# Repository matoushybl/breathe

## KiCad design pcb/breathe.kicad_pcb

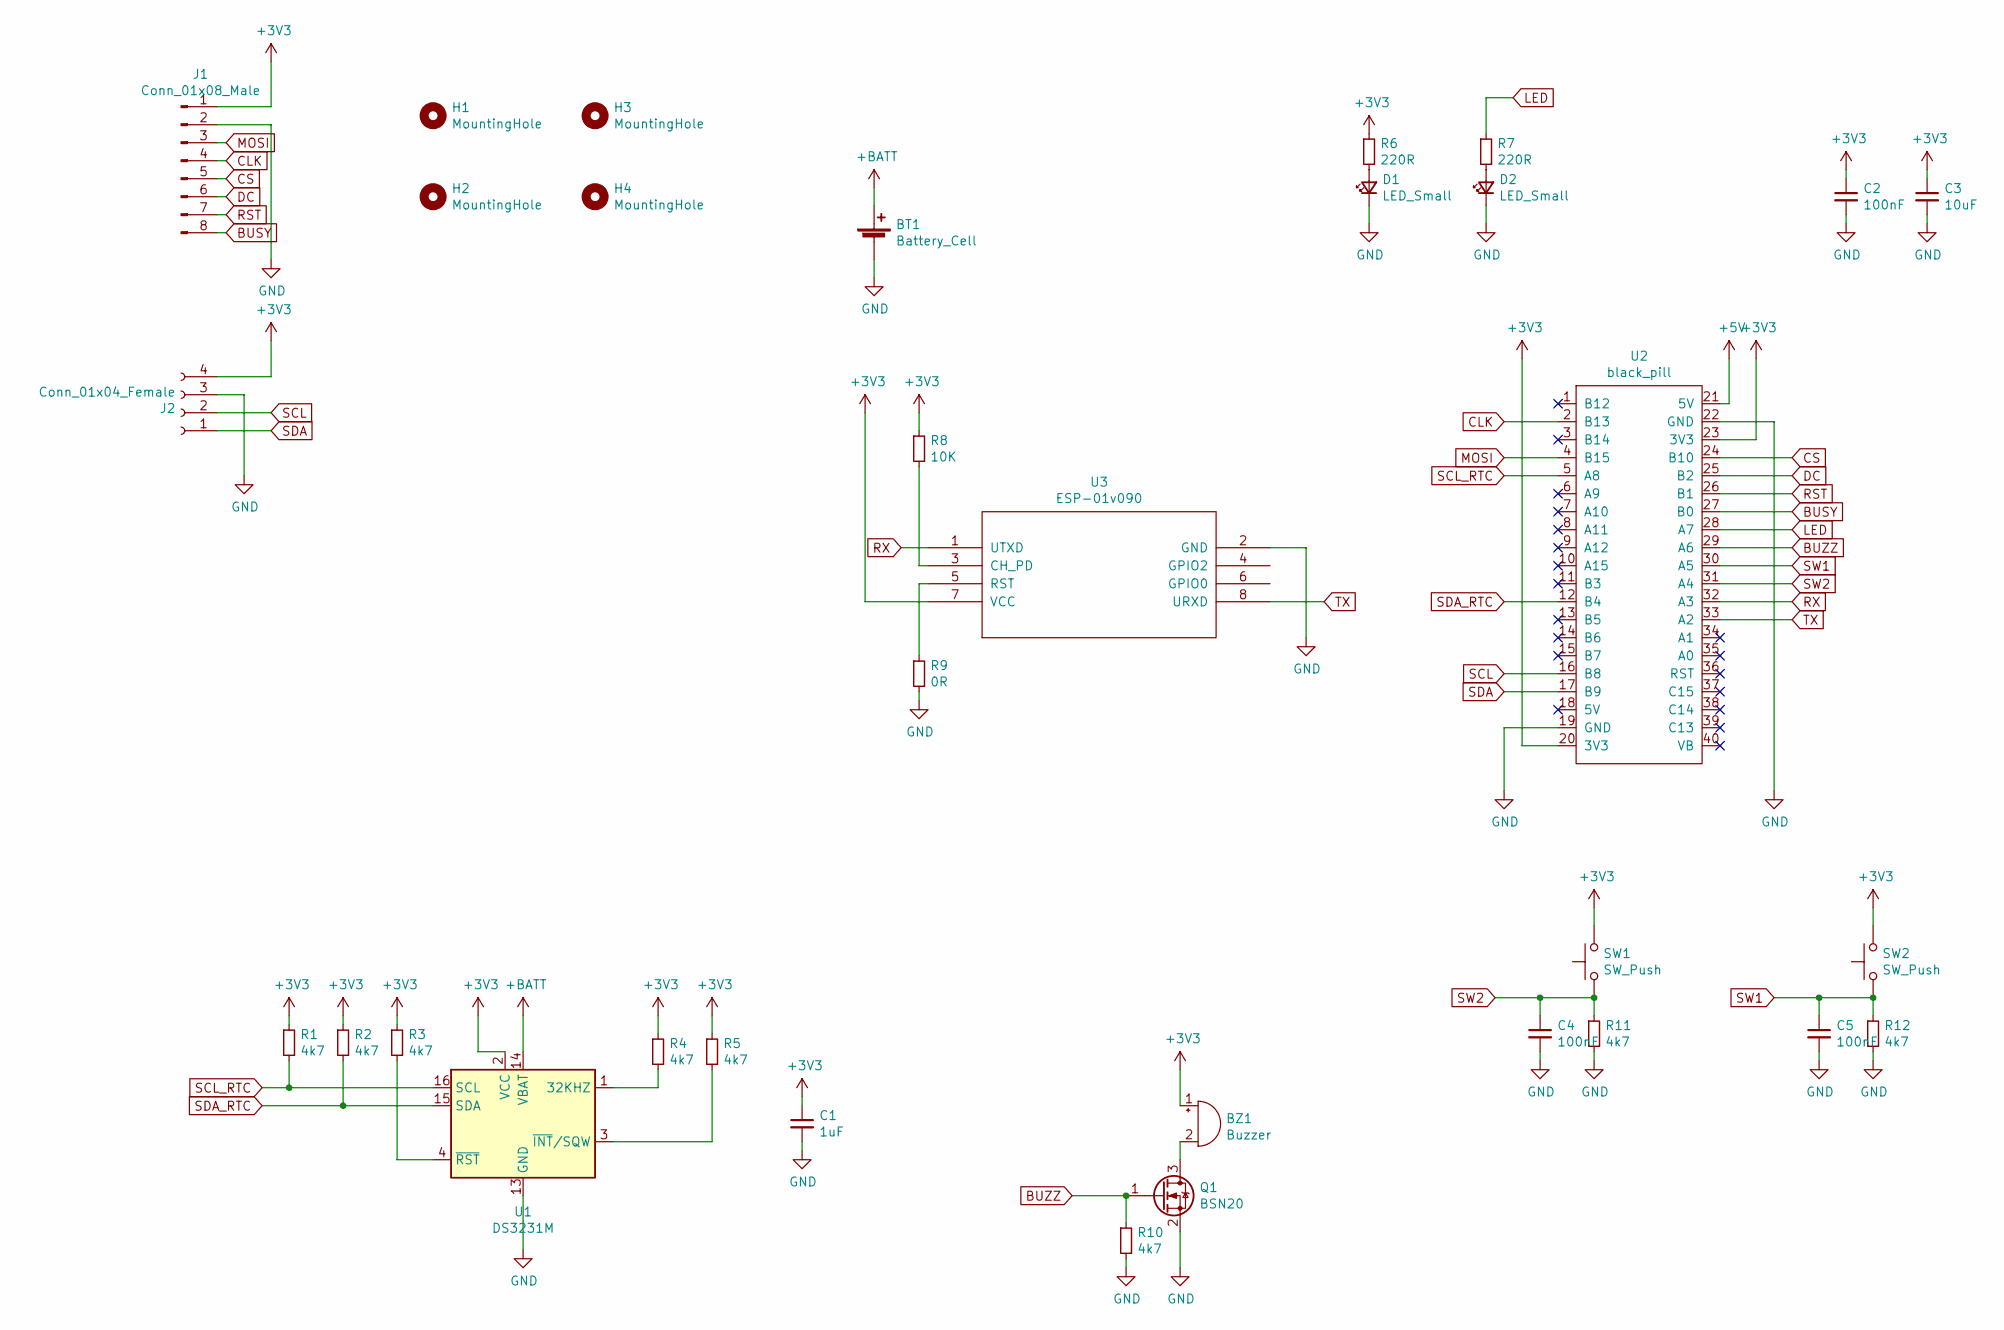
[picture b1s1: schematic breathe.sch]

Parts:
BT1: Battery_Cell; BatteryHolder_Keystone_1060_1x2032
BZ1: Buzzer; Buzzer_12x9.5RM7.6
C1: 1uF; C_0805_2012Metric_Pad1.18x1.45mm_HandSolder
C2, C4, C5: 100nF; C_0805_2012Metric_Pad1.18x1.45mm_HandSolder
C3: 10uF; C_0805_2012Metric_Pad1.18x1.45mm_HandSolder
D1, D2: LED_Small; LED_0805_2012Metric_Pad1.15x1.40mm_HandSolder
H1, H2, H3, H4: MountingHole; MountingHole_2.7mm_M2.5
J1: Conn_01x08_Male; PinHeader_1x08_P2.54mm_Vertical
J2: Conn_01x04_Female; PinHeader_1x04_P2.54mm_Horizontal
Q1: BSN20; SOT-23
R1, R2, R3, R4, R5, R10, R11, R12: 4k7; R_0805_2012Metric_Pad1.20x1.40mm_HandSolder
R6, R7: 220R; R_0805_2012Metric_Pad1.20x1.40mm_HandSolder
R8: 10K; R_0805_2012Metric_Pad1.20x1.40mm_HandSolder
R9: 0R; R_0805_2012Metric_Pad1.20x1.40mm_HandSolder
SW1, SW2: SW_Push; SW_PUSH_6mm
U1: DS3231M; SOIC-16W_7.5x10.3mm_P1.27mm
U2: black_pill
U3: ESP-01v090; ESP-01

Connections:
+3V3: BZ1.1 (-), C1.1, C2.1, C3.1, J1.1, J2.4, R1.1, R2.1, R3.1, R4.1, R5.1, R6.1, R8.1, SW1.2, SW2.2, U1.2 (VCC), U2.20 (3V3), U2.23 (3V3), U3.7 (VCC)
+BATT: BT1.1 (+), U1.14 (VBAT)
BUSY: J1.8, U2.27 (B0)
BUZZ: Q1.1 (G), R10.1, U2.29 (A6)
CLK: J1.4, U2.2 (B13)
CS: J1.5, U2.24 (B10)
DC: J1.6, U2.25 (B2)
GND: BT1.2 (-), C1.2, C2.2, C3.2, C4.2, C5.2, D1.1 (K), D2.1 (K), J1.2, J2.3, Q1.2 (S), R9.2, R10.2, R11.2, R12.2, U1.5 (GND), U1.6 (GND), U1.7 (GND), U1.8 (GND), U1.9 (GND), U1.10 (GND), U1.11 (GND), U1.12 (GND), U1.13 (GND), U2.19 (GND), U2.22 (GND), U3.2 (GND)
LED: R7.1, U2.28 (A7)
MOSI: J1.3, U2.4 (B15)
unnamed: BZ1.2 (+), Q1.3 (D)
unnamed: D1.2 (A), R6.2
unnamed: D2.2 (A), R7.2
unnamed: R3.2, U1.4 (~RST)
unnamed: R4.2, U1.1 (32KHZ)
unnamed: R5.2, U1.3 (~INT~/SQW)
unnamed: R8.2, U3.3 (CH_PD)
unnamed: R9.1, U3.5 (RST)
RST: J1.7, U2.26 (B1)
RX: U2.32 (A3), U3.1 (UTXD)
SCL: J2.2, U2.16 (B8)
SCL_RTC: R1.2, U1.16 (SCL), U2.5 (A8)
SDA: J2.1, U2.17 (B9)
SDA_RTC: R2.2, U1.15 (SDA), U2.12 (B4)
SW1: C5.1, R12.1, SW2.1, U2.30 (A5)
SW2: C4.1, R11.1, SW1.1, U2.31 (A4)
TX: U2.33 (A2), U3.8 (URXD)

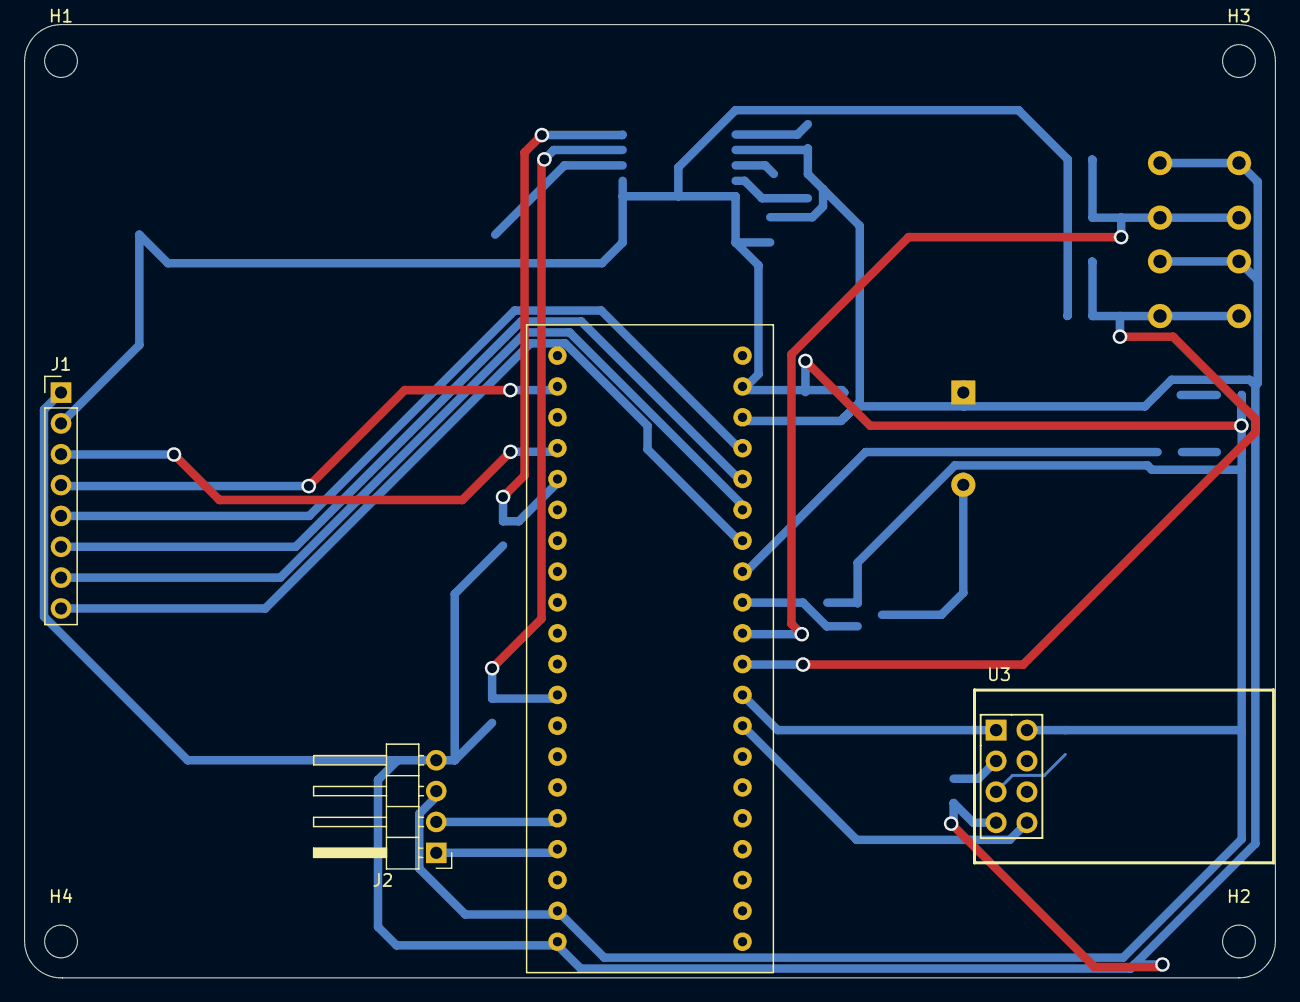
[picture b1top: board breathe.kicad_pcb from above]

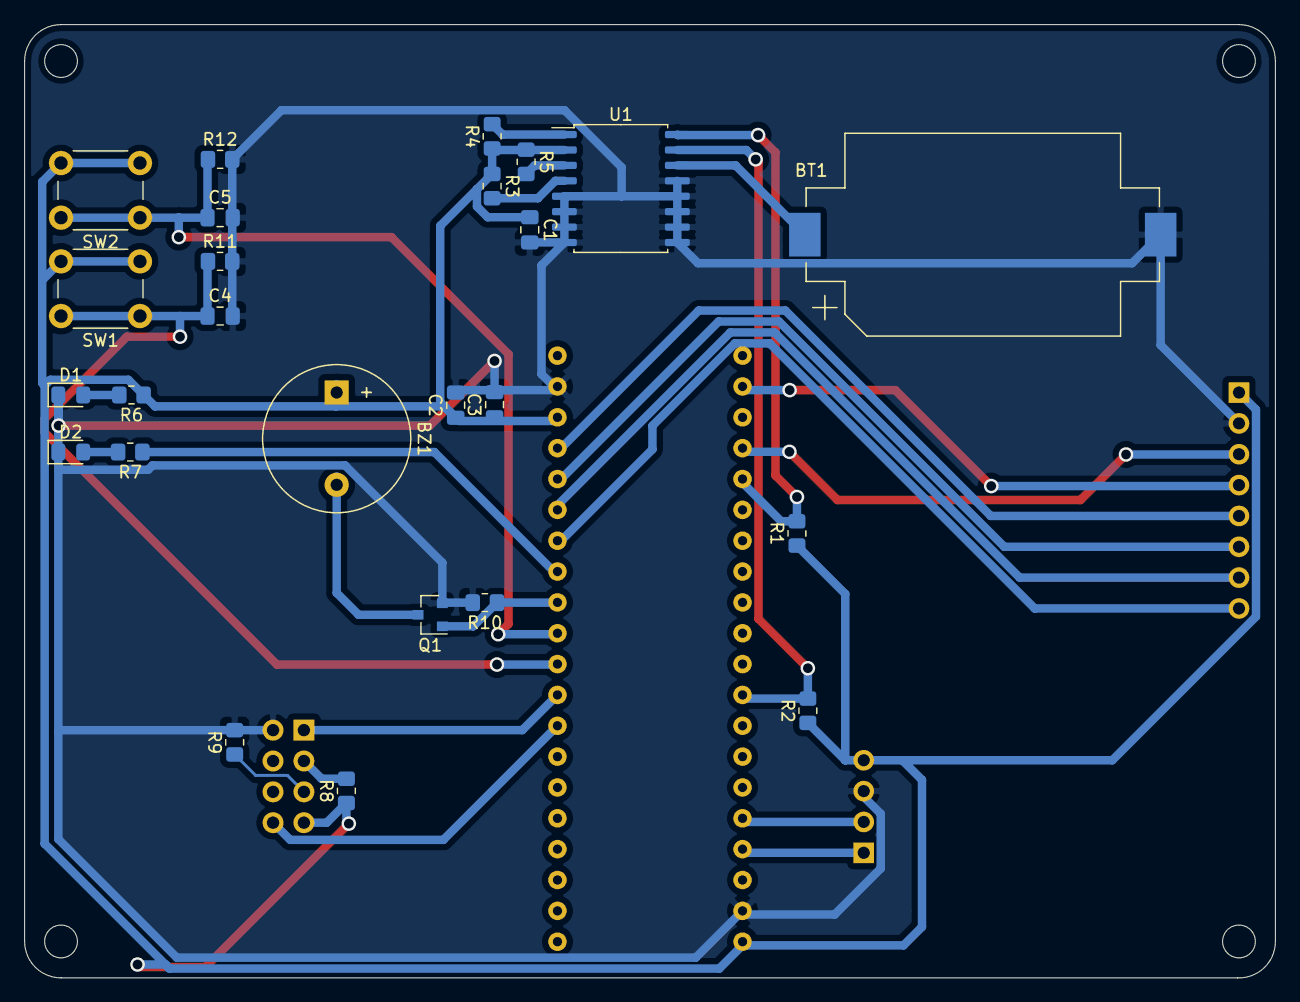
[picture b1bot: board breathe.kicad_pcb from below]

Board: 2 copper layers, 103.0 x 78.5 mm, 33 parts (25 on the bottom side), 27 nets.

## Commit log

2020-11-18 Initial commit.
2020-11-19 WIP - tasks
2020-11-19 Finish porting from nrf.
2020-11-20 Add c02 image indicator.
2020-11-29 Add RTC and time displaying, add averaging of measured values.
2020-12-14 Add setting time using USB.
2020-12-19 Add pcb and control program.
2020-12-21 Add beeper.
